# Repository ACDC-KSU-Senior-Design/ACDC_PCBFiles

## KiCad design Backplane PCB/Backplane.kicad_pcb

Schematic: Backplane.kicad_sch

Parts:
C1: .47u; C_0805_2012Metric
C2: 0.1u; C_0603_1608Metric
C3: 3.3n; C_0603_1608Metric
C4: 33u; C_1206_3216Metric
C5, C6: 22u; C_1206_3216Metric
C7, C8, C9, C10, C11, C12, C13, C14, C15, C16, C17, C18, C19, C20, C21, C22, C23: 10u; C_1206_3216Metric
CR1: SMDJ85A
CR6, CR8, CR10, CR12, CR14, CR16, CR18, CR19, CR20, CR24, CR25, CR26: SMDJ33A
CR27, CR28, CR29, CR30, CR31: SMDJ6.0A; SMDJ6_0A
CR32: RF201LAM2STR; RF201LAM2STR(new_POW_diode)
CR33, CR34, CR35, CR36, CR37, CR38, CR39, CR40, CR41, CR42, CR43, CR44: RBR1MM60ATFTR; RBR1MM60ATFTR(new_VR_diode)
D1: 1N5818; D_DO-41_SOD81_P10.16mm_Horizontal
D2, D3, D4, D5, D6, D7, D8, D9, D10, D11, D12, D15: 1N4148WS
D27, D28, D29, D30, D31, D32, D33, D34, D35, D36: 1N5819HW-7-F; 1N5819; PARTREV 18-2
D37, D38, D39, D40, D41, D42: SMDJ60CA; SMDJ6_0CA; PARTREV R2102
H1, H2, H3, H4, H5, H6, H7: MountingHole; MountingHole_3.2mm_M3
J1, J2, J3, J4, J5: 10018783-10202TLF; PCI_Express_Card; PARTREV AA
J6: 5019514000; BP_Connector
L1: 22u; IND_1210-WE-PD_WRE
R1, R4: 30k; R_0805_2012Metric
R2: 20m; R_1206_3216Metric
R3, R81: 200k; R_0805_2012Metric
R5, R7, R55, R56, R57, R58, R59, R60: 10k; R_0805_2012Metric
R6, R24: 15k; R_0805_2012Metric
R8, R10, R50, R51, R52, R53, R54: 100k; R_0805_2012Metric
R9, R11: 10; R_0805_2012Metric
R12, R69, R70, R71, R72, R73, R74, R75, R76, R77, R78, R79, R84: 2k; R_0805_2012Metric
R13, R15, R17, R19, R21, R23, R27, R29, R31, R33, R35, R37, R38, R39, R40, R41, R42, R43, R44, R45, R46, R47, R48, R49, R86, R87, R88, R89, R90, R92, R94, R95, R99, R100: 1k; R_0805_2012Metric
R14, R16, R18, R20, R22, R26, R28, R30, R32, R34, R36, R68, R83: 3k; R_0805_2012Metric
R25: 4.7k; R_0805_2012Metric
R61, R63: 2.2k; R_0805_2012Metric
R62, R64, R65: 200; R_0402_1005Metric
R66, R67: 2; R_0603_1608Metric
R80, R82: 22k; R_0805_2012Metric
R85: 1.5k; R_0805_2012Metric
U1: LTC3894EFE-PBF; TSSOP20-EP_4P4X6P5_ADI
U2: FDS4435A; SOIC8_751EB_FAS
U3, U4, U5, U6, U7, U8, U11, U12, U13, U14, U15, U16: ISP817CXSM; ISP817SM_ISO
U9, U10: ADP7104ACPZ-R7; CP_8_5_ADI
U17, U18, U19, U20, U21: OP191GSZ-REEL7; OP191

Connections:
3V3: C5.2, C8.1, C9.1, C10.1, C11.1, C12.1, C13.1, R6.2, R8.2, R9.2, U3.4, U4.4, U5.4, U6.4, U7.4, U8.4, U9.1 (VOUT)
5.5V: C6.2, C7.1, C20.1, C21.1, C22.1, C23.1, D28.C, D30.C, D32.C, D34.C, D36.C, R10.2, R11.2, R24.2, U10.1 (VOUT), U17.7 (+V), U18.7 (+V), U19.7 (+V), U20.7 (+V), U21.7 (+V)
28V_REF: C1.1, C14.1, C15.1, C16.1, C17.1, C18.1, C19.1, CR1.1, CR32.1, D2.C, D4.C, D6.C, D7.C, D9.C, D11.C, J6.17, R5.2, U1.3 (RUN), U1.20 (VIN), U2.8, U11.4, U12.4, U13.4, U14.4, U15.4, U16.4
A429_IN+: D38.2, J1.A11, J1.B11, J2.A11, J2.B11, J3.A11, J3.B11, J4.A11, J4.B11, J5.A11, J5.B11, J6.11, R56.2
A429_IN-: D37.2, J1.A10, J1.B10, J2.A10, J2.B10, J3.A10, J3.B10, J4.A10, J4.B10, J5.A10, J5.B10, J6.10, R55.2
A429_OUT+: D39.2, J1.A12, J1.B12, J2.A12, J2.B12, J3.A12, J3.B12, J4.A12, J4.B12, J5.A12, J5.B12, J6.12, R57.2
A429_OUT-: D40.2, J1.A13, J1.B13, J2.A13, J2.B13, J3.A13, J3.B13, J4.A13, J4.B13, J5.A13, J5.B13, J6.13, R58.2
BPOW: C4.1, J1.A17, J1.B17, J2.A17, J2.B17, J3.A17, J3.B17, J4.A17, J4.B17, J5.A17, J5.B17, R2.1, R3.2, U1.6 (SENSE-), U9.5 (EN/UVLO), U9.8 (VIN), U10.5 (EN/UVLO), U10.8 (VIN)
CANHI: J1.A7, J1.B7, J2.A7, J2.B7, J3.A7, J3.B7, J4.A7, J4.B7, J5.A7, J5.B7
CANLO: J1.A8, J1.B8, J2.A8, J2.B8, J3.A8, J3.B8, J4.A8, J4.B8, J5.A8, J5.B8
DAC_OUT: J1.A5, J1.B5, J2.A5, J2.B5, J3.A5, J3.B5, J4.A5, J4.B5, J5.A5, J5.B5, U21.2 (-INA), U21.6 (OUTA)
DI1: CR6.1, CR33.1, J6.19, R39.2, R68.2
DI2: CR10.1, CR34.1, J6.20, R14.2, R41.2
DI3: CR14.1, CR35.1, J6.21, R16.2, R43.2
DI4: CR8.1, CR36.1, J6.22, R18.2, R40.2
DI5: CR12.1, CR37.1, J6.23, R20.2, R42.2
DI6: CR16.1, CR38.1, J6.24, R22.2, R44.2
DO1: CR18.1, CR39.1, J6.27, R27.2, R38.2, U11.3
DO2: CR19.1, CR40.1, J6.28, R29.2, R45.2, U12.3
DO3: CR20.1, CR41.1, J6.29, R31.2, R46.2, U13.3
DO4: CR24.1, CR42.1, J6.30, R33.2, R47.2, U14.3
DO5: CR25.1, CR43.1, J6.31, R35.2, R48.2, U15.3
DO6: CR26.1, CR44.1, J6.32, R37.2, R49.2, U16.3
DOFB1: J1.A27, J1.B27, J2.A27, J2.B27, J3.A27, J3.B27, J4.A27, J4.B27, J5.A27, J5.B27, R26.2
DOFB2: J1.A28, J1.B28, J2.A28, J2.B28, J3.A28, J3.B28, J4.A28, J4.B28, J5.A28, J5.B28, R28.2
DOFB3: J1.A29, J1.B29, J2.A29, J2.B29, J3.A29, J3.B29, J4.A29, J4.B29, J5.A29, J5.B29, R30.2
DOFB4: J1.A30, J1.B30, J2.A30, J2.B30, J3.A30, J3.B30, J4.A30, J4.B30, J5.A30, J5.B30, R32.2
DOFB5: J1.A31, J1.B31, J2.A31, J2.B31, J3.A31, J3.B31, J4.A31, J4.B31, J5.A31, J5.B31, R34.2
DOFB6: J1.A32, J1.B32, J2.A32, J2.B32, J3.A32, J3.B32, J4.A32, J4.B32, J5.A32, J5.B32, R36.2
DSI1: J1.A19, J1.B19, J2.A19, J2.B19, J3.A19, J3.B19, J4.A19, J4.B19, J5.A19, J5.B19, R13.2, U3.3
DSI2: J1.A20, J1.B20, J2.A20, J2.B20, J3.A20, J3.B20, J4.A20, J4.B20, J5.A20, J5.B20, R15.2, U4.3
DSI3: J1.A21, J1.B21, J2.A21, J2.B21, J3.A21, J3.B21, J4.A21, J4.B21, J5.A21, J5.B21, R17.2, U5.3
DSI4: J1.A22, J1.B22, J2.A22, J2.B22, J3.A22, J3.B22, J4.A22, J4.B22, J5.A22, J5.B22, R19.2, U6.3
DSI5: J1.A23, J1.B23, J2.A23, J2.B23, J3.A23, J3.B23, J4.A23, J4.B23, J5.A23, J5.B23, R21.2, U7.3
DSI6: J1.A24, J1.B24, J2.A24, J2.B24, J3.A24, J3.B24, J4.A24, J4.B24, J5.A24, J5.B24, R23.2, U8.3
GND: C2.2, C3.2, C4.2, C5.1, C6.1, C7.2, C8.2, C9.2, C10.2, C11.2, C12.2, C13.2, C14.2, C15.2, C16.2, C17.2, C18.2, C19.2, C20.2, C21.2, C22.2, C23.2, CR1.2, CR6.2, CR8.2, CR10.2, CR12.2, CR14.2, CR16.2, CR18.2, CR19.2, CR20.2, CR24.2, CR25.2, CR26.2, CR27.2, CR28.2, CR29.2, CR30.2, CR31.2, CR32.2, CR33.2, CR34.2, CR35.2, CR36.2, CR37.2, CR38.2, CR39.2, CR40.2, CR41.2, CR42.2, CR43.2, CR44.2, D1.2 (A), D3.A, D5.A, D8.A, D10.A, D12.A, D15.A, D27.A, D29.A, D31.A, D33.A, D35.A, D37.1, D38.1, D39.1, D40.1, D41.1, D42.1, J1.A6, J1.A9, J1.A16, J1.A18, J1.A25, J1.A26, J1.A33, J1.B6, J1.B9, J1.B16, J1.B18, J1.B25, J1.B26, J1.B33, J2.A6, J2.A9, J2.A16, J2.A18, J2.A25, J2.A26, J2.A33, J2.B6, J2.B9, J2.B16, J2.B18, J2.B25, J2.B26, J2.B33, J3.A6, J3.A9, J3.A16, J3.A18, J3.A25, J3.A26, J3.A33, J3.B6, J3.B9, J3.B16, J3.B18, J3.B25, J3.B26, J3.B33, J4.A6, J4.A9, J4.A16, J4.A18, J4.A25, J4.A26, J4.A33, J4.B6, J4.B9, J4.B16, J4.B18, J4.B25, J4.B26, J4.B33, J5.A6, J5.A9, J5.A16, J5.A18, J5.A25, J5.A26, J5.A33, J5.B6, J5.B9, J5.B16, J5.B18, J5.B25, J5.B26, J6.6, J6.7, J6.8, J6.9, J6.16, J6.18, J6.25, J6.26, J6.33, R5.1, R7.1, R13.1, R15.1, R17.1, R19.1, R21.1, R23.1, R27.1, R29.1, R31.1, R33.1, R35.1, R37.1, R38.1, R39.1, R40.1, R41.1, R42.1, R43.1, R44.1, R45.1, R46.1, R47.1, R48.1, R49.1, R50.1, R51.1, R52.1, R53.1, R54.1, R55.1, R56.1, R57.1, R58.1, R59.1, R60.1, R65.1, R66.1, R67.1, R80.1, R85.2, R86.1, R87.1, R88.1, R89.1, R90.1, R92.1, R94.1, R95.1, R99.1, R100.1, U1.11 (PLLIN/MODE), U1.14 (OVLO), U1.15 (EXTS), U3.2, U4.2, U5.2, U6.2, U7.2, U8.2, U9.3 (GND), U9.6 (GND), U9.9 (EPAD), U10.3 (GND), U10.6 (GND), U10.9 (EPAD), U11.2, U12.2, U13.2, U14.2, U15.2, U16.2, U17.4 (-V), U18.4 (-V), U19.4 (-V), U20.4 (-V), U21.4 (-V)
unnamed: D1.1 (K), L1.2, U2.3
unnamed: D2.A, D3.C, R12.1, U3.1
unnamed: D4.A, D5.C, R70.1, U5.1
unnamed: D7.A, D8.C, R71.1, U6.1
unnamed: D9.A, D10.C, R72.1, U7.1
unnamed: D11.A, D12.C, R73.1, U8.1
unnamed: D6.A, D15.C, R69.1, U4.1
unnamed: D27.C, D28.A
unnamed: D29.C, D30.A
unnamed: D31.C, D32.A
unnamed: D33.C, D34.A
unnamed: D35.C, D36.A
unnamed: J1.A34, R86.2
unnamed: J1.A35, R87.2
unnamed: J1.A36, R88.2
unnamed: J2.A34, R89.2
unnamed: J2.A35, R90.2
unnamed: J3.A34, R92.2
unnamed: J3.A36, R94.2
unnamed: J4.A34, R95.2
unnamed: J5.A35, R99.2
unnamed: J5.A36, R100.2
unnamed: R1.2, R83.1
unnamed: R3.1, R81.2
unnamed: R4.1, R80.2
unnamed: R6.1, R61.2
unnamed: R11.1, R67.2
unnamed: R12.2, R68.1
unnamed: R14.1, R69.2
unnamed: R16.1, R70.2
unnamed: R18.1, R71.2
unnamed: R20.1, R72.2
unnamed: R22.1, R73.2
unnamed: R24.1, R63.2
unnamed: R25.1, R65.2
unnamed: R26.1, R79.2
unnamed: R28.1, R78.2
unnamed: R30.1, R77.2
unnamed: R32.1, R76.2
unnamed: R34.1, R75.2
unnamed: R36.1, R74.2
unnamed: R61.1, R62.2
unnamed: R63.1, R64.2
unnamed: R9.1, R66.2
unnamed: R74.1, U16.1
unnamed: R75.1, U15.1
unnamed: R76.1, U14.1
unnamed: R77.1, U13.1
unnamed: R78.1, U12.1
unnamed: R79.1, U11.1
unnamed: R81.1, R82.2
unnamed: R83.2, R84.1
unnamed: R84.2, R85.1
unnamed: C1.2, U1.18 (CAP)
unnamed: R1.1, U1.13 (FREQ)
unnamed: U1.1 (GATE), U2.4
unnamed: C3.1, U1.7 (ITH)
unnamed: R4.2, R82.1, U1.8 (PGUV), U1.9 (VFB)
unnamed: L1.1, R2.2, U1.5 (SENSE+)
unnamed: C2.1, U1.10 (TRACK/SS)
unnamed: R8.1, U9.7 (PG)
unnamed: R7.2, R62.1, U9.2 (SENSE/ADJ)
unnamed: R10.1, U10.7 (PG)
unnamed: R25.2, R64.1, U10.2 (SENSE/ADJ)
unnamed: CR27.1, J6.1, R50.2, U17.3 (+INA)
unnamed: CR28.1, J6.2, R51.2, U18.3 (+INA)
unnamed: CR29.1, J6.3, R52.2, U19.3 (+INA)
unnamed: CR30.1, J6.4, R53.2, U20.3 (+INA)
unnamed: CR31.1, J6.5, R54.2, U21.3 (+INA)
RTD+IN: J1.A4, J1.B4, J2.A4, J2.B4, J3.A4, J3.B4, J4.A4, J4.B4, J5.A4, J5.B4, U20.2 (-INA), U20.6 (OUTA)
RTD-IN: J1.A3, J1.B3, J2.A3, J2.B3, J3.A3, J3.B3, J4.A3, J4.B3, J5.A3, J5.B3, U19.2 (-INA), U19.6 (OUTA)
SIN1: D41.2, J1.A14, J1.B14, J2.A14, J2.B14, J3.A14, J3.B14, J4.A14, J4.B14, J5.A14, J5.B14, J6.14, R59.2
SIN2: D42.2, J1.A15, J1.B15, J2.A15, J2.B15, J3.A15, J3.B15, J4.A15, J4.B15, J5.A15, J5.B15, J6.15, R60.2
TD+IN: J1.A2, J1.B2, J2.A2, J2.B2, J3.A2, J3.B2, J4.A2, J4.B2, J5.A2, J5.B2, U18.2 (-INA), U18.6 (OUTA)
TD-IN: J1.A1, J1.B1, J2.A1, J2.B1, J3.A1, J3.B1, J4.A1, J4.B1, J5.A1, J5.B1, U17.2 (-INA), U17.6 (OUTA)

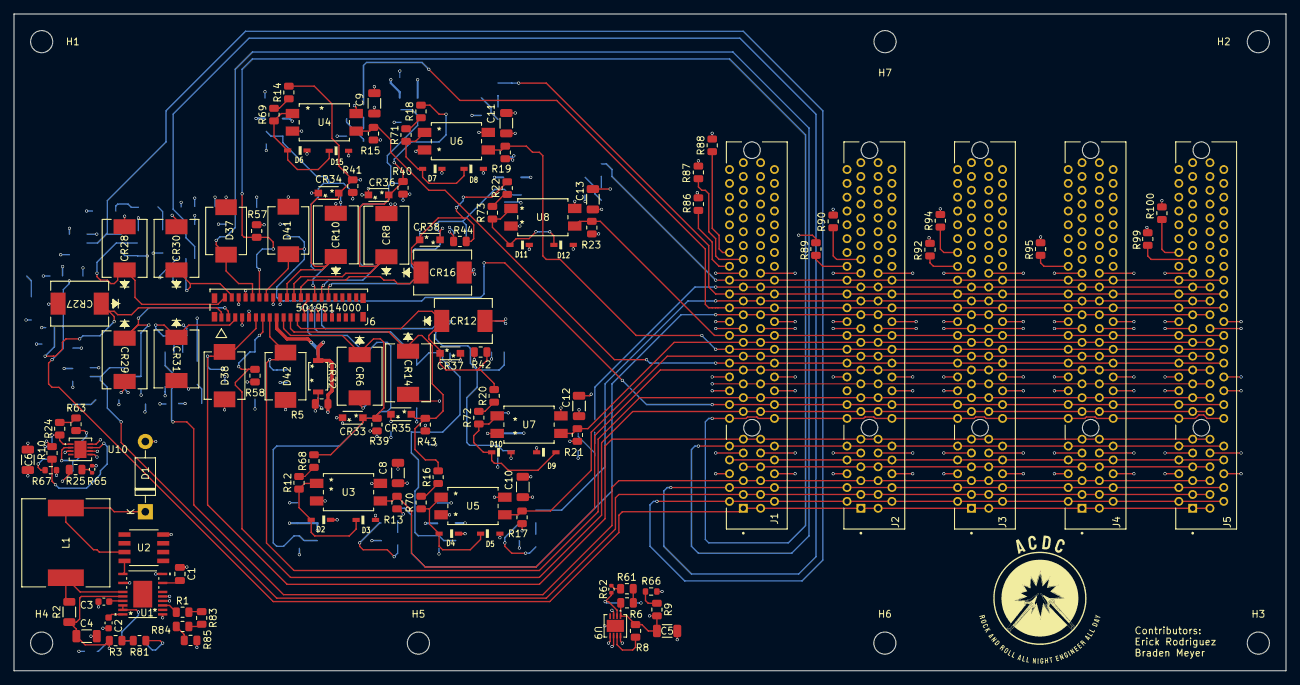
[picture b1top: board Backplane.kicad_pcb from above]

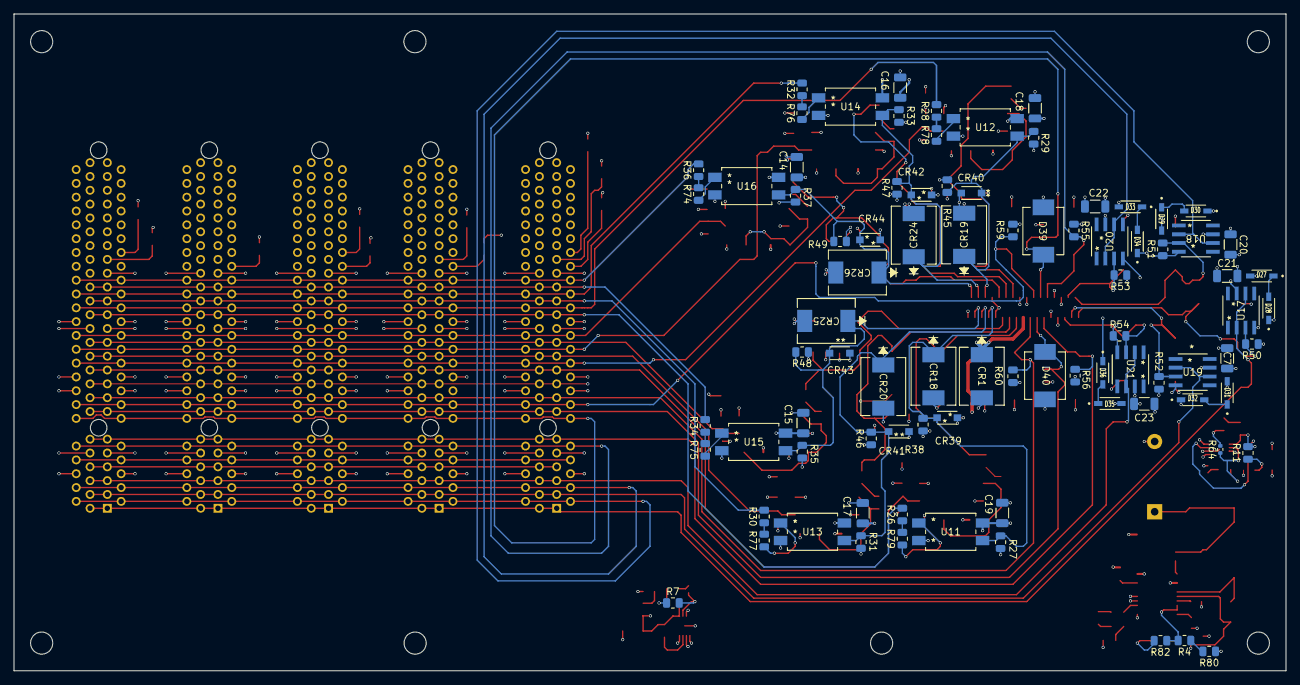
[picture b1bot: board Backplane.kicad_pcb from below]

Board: 4 copper layers, 184.0 x 95.0 mm, 213 parts (86 on the bottom side), 111 nets.

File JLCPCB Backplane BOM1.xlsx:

Comment | Designator | Footprint | JLCPCB Part #（optional）
3.3nF | C3 | C_0603_1608Metric | C1613
.47uF | C1 | C_0805_2012Metric | C13967
0.1uF | C2 | C_0603_1608Metric | C14663
10uF | C10,C8,C11,C9,C13,C12,C15,C22,C7,C16,C20,C19,C23,C14,C21,C18,C17 | C_1206_3216Metric | C13585
22uF | C6,C5 | C_1206_3216Metric | C12891
33uF | C4 | C_1206_3216Metric | C524627
20m | R2 | R_1206_3216Metric | C2765435
2 | R67,R66 | R_0603_1608Metric | C22977
10 | R9,R11 | R_0805_2012Metric | C17415
200 | R62,R65,R64 | R_0402_1005Metric | C25087
1k | R38,R39,R40,R41,R42,R43,R44,R45,R46,R47,R48,R49, R99,R94,R13,R23,R100,R88,R17,R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 | R_0805_2012Metric | C17513
1.5k | R85 | R_0805_2012Metric | C4310
2k | R71,R72,R70,R84,R69,R12,R73,R74,R75,R77,R79,R76,R78 | R_0805_2012Metric | C17604
2.2k | R63,R61 | R_0805_2012Metric | C17520
3k | R18,R20,R22,R16,R68,R83,R14,R32,R34,R30,R28,R26,R36 | R_0805_2012Metric | C17661
4.7k | R25 | R_0805_2012Metric | C17673
10k | R7,R5,R58,R57,R55,R56,R60,R59 | R_0805_2012Metric | C174414
15k | R24,R6 | R_0805_2012Metric | C17475
22k | R82,R80 | R_0805_2012Metric | C17560
30k | R1,R4 | R_0805_2012Metric | C17621
100k | R10,R8,R50,R51,R54,R52,R53 | R_0805_2012Metric | C149504
200k | R81,R3 | R_0805_2012Metric | C17539
22uH | L1 | 22uH_IND
5019514000 | J6 | BP_Connector | C493441
1N4148WS | D8,D4,D11,D5,D12,D3,D7,D10,D6,D15,D9,D2 | 1N4148WS | C2128
1N5818 | D1 | D_DO-41_SOD81_P10.16mm_Horizontal | C402217
1N5819HW-7-F | D34,D29,D28,D33,D30,D31,D35,D27,D36,D32 | 1N5819 | C82544
ADP7104ACPZ-R7 | U9,U10 | CP_8_5_ADI | C514351
FDS4435A | U2 | SOIC8_751EB_FAS | C5122021
LTC3894EFE-PBF | U1 | TSSOP20-EP_4P4X6P5_ADI | C580815
RF201LAM2STR | CR32 | RF201LAM2STR(new_POW_diode) | C509969
SMDJ33A | CR16,CR6,CR8,CR10,CR14,CR12,CR25,CR19,CR24,CR26,CR20,CR18 | SMDJ33A | C438163
SMDJ6.0A | CR31,CR27,CR30,CR28,CR29 | SMDJ6_0A | C152070
SMDJ6.0CA | D38,D41,D42,D37,D40,D39 | SMDJ6_0CA | C310142
SMDJ85A | CR1 | SMDJ85A | C2990381
LTV-816S-TA1-B | U6,U5,U7,U3,U4,U8,U12,U16,U13,U15,U14,U11 | ISP817SM_ISO | C115456
OP191GSZ-REEL7 | U17,U21,U19,U18,U20 | OP191
RBR1MM60ATFTR | CR35,CR38,CR36,CR37,CR33,CR34,CR43,CR44,CR41,CR39,CR42,CR40 | RBR1MM60ATFTR(new_VR_diode)
10018783-10202TLF | J5,J1,J2,J4,J3 | PCI_Express_Card

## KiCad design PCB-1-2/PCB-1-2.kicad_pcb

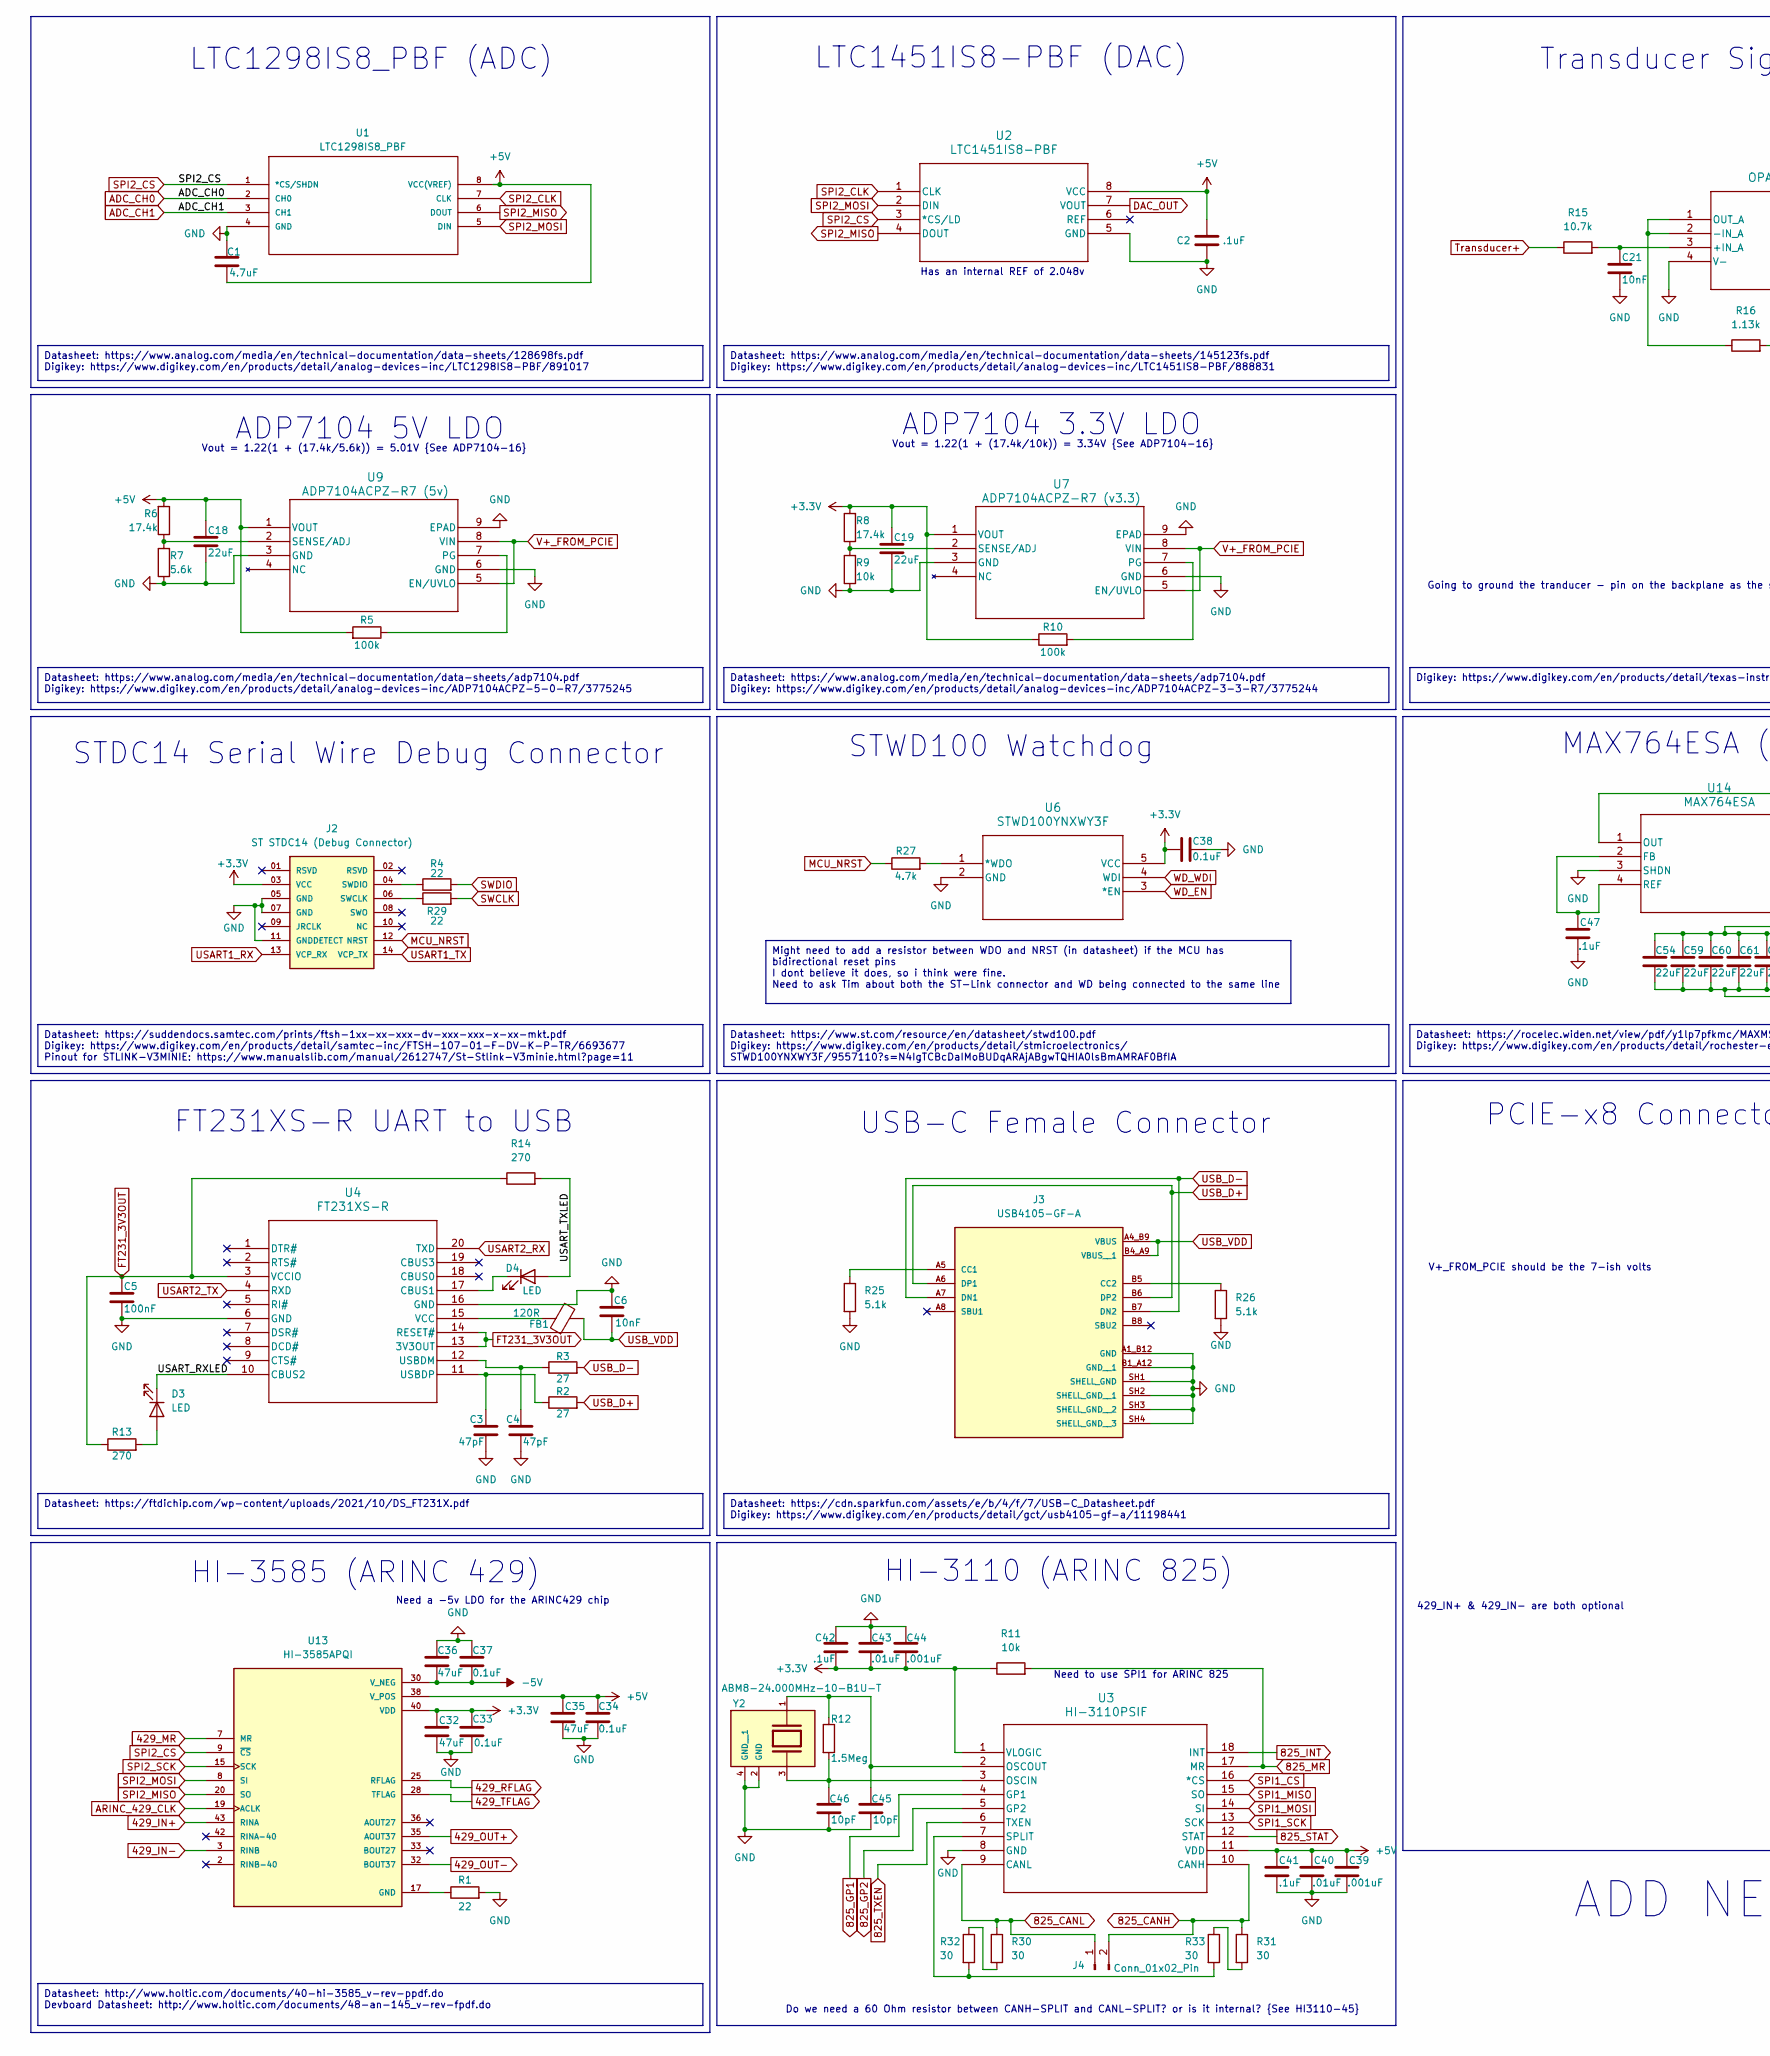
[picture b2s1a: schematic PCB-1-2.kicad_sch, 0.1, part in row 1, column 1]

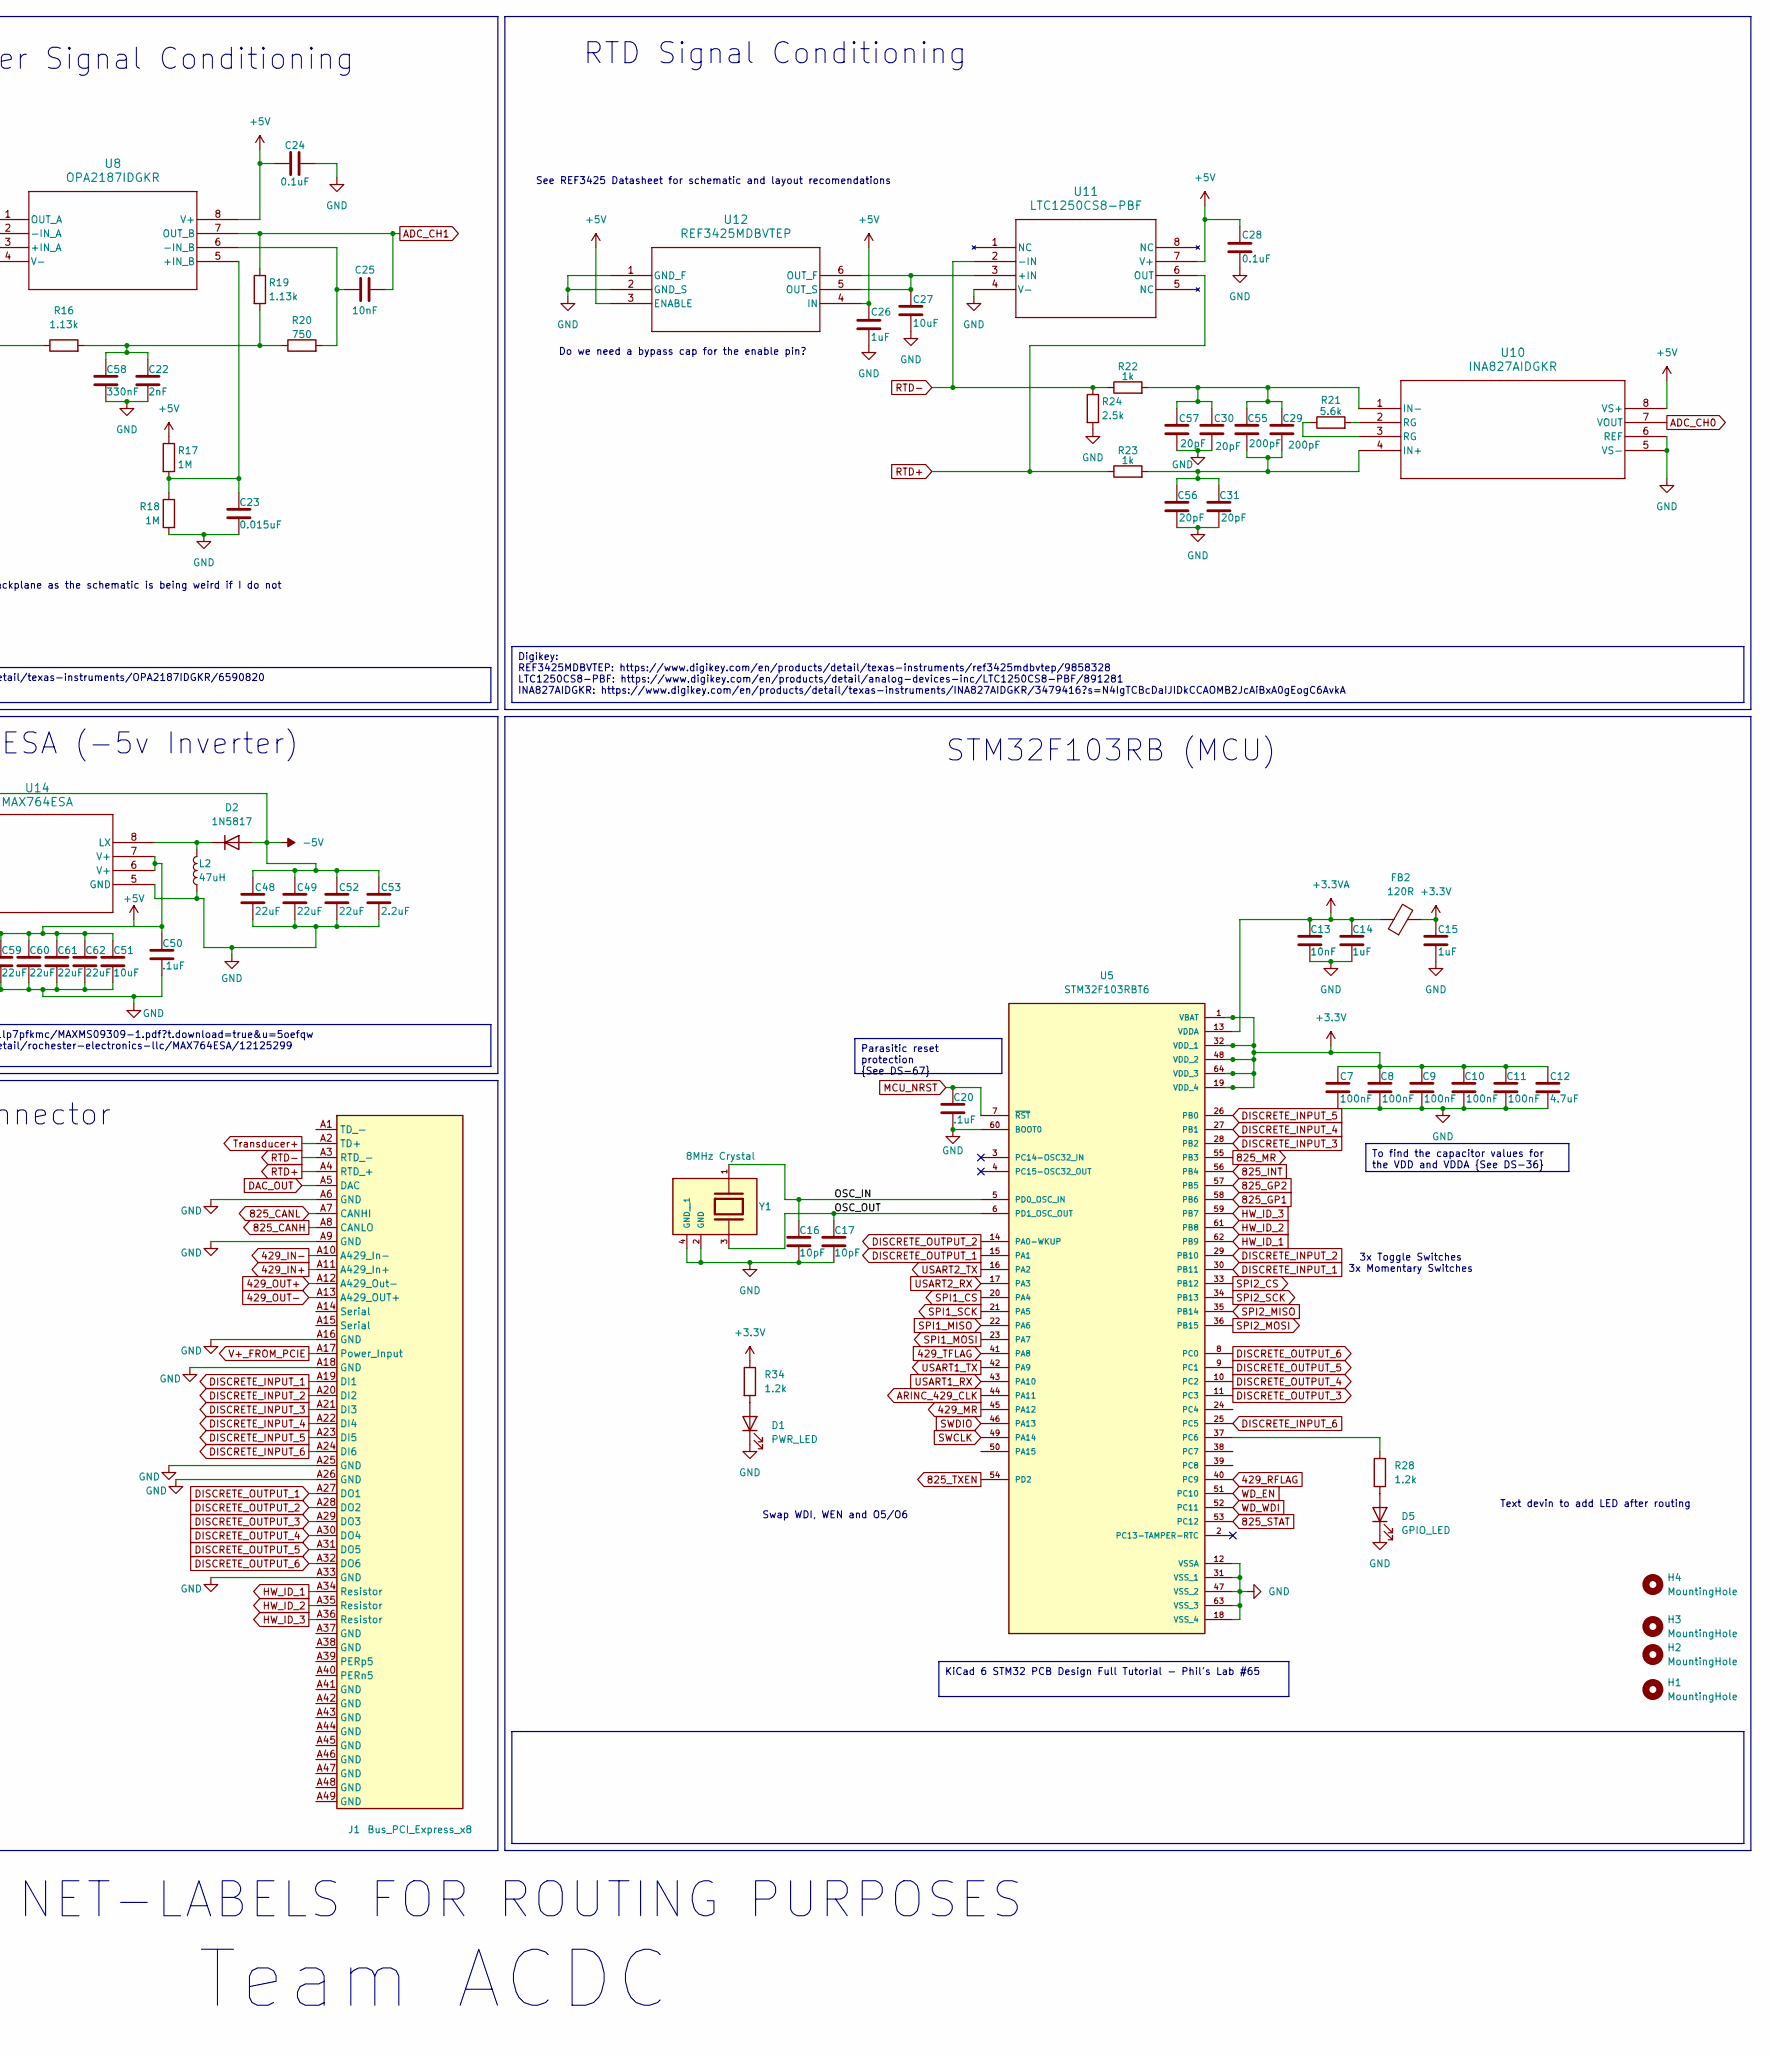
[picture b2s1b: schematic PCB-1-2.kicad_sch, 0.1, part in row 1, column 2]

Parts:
C1, C12: 4.7uF; C_0805_2012Metric
C2, C20, C41, C42: .1uF; C_0805_2012Metric
C3, C4: 47pF; C_0805_2012Metric
C5, C7, C8, C9, C10, C11: 100nF; C_0805_2012Metric
C6, C13, C21, C25: 10nF; C_0805_2012Metric
C14, C15, C26: 1uF; C_0805_2012Metric
C16, C17, C45, C46: 10pF; C_0805_2012Metric
C18, C19, C48, C49, C52, C54, C59, C60, C61, C62: 22uF; C_0805_2012Metric
C22: 2nF; C_0603_1608Metric
C23: 0.015uF; C_0402_1005Metric
C24, C28, C33, C34, C37, C38: 0.1uF; C_0805_2012Metric
C27: 10uF; C_0805_2012Metric
C29, C55: 200pF; C_0603_1608Metric
C30, C31, C56, C57: 20pF; C_0805_2012Metric
C32, C35, C36: 47uF; C_0805_2012Metric
C39, C44: .001uF; C_0805_2012Metric
C40, C43: .01uF; C_0805_2012Metric
C47, C50: .1uF; C_0603_1608Metric
C51: 10uF; C_1206_3216Metric
C53: 2.2uF; C_0805_2012Metric
C58: 330nF; C_0805_2012Metric
D1: PWR_LED; LED_0805_2012Metric
D2: 1N5817
D3, D4: LED; LED_0805_2012Metric
D5: GPIO_LED; LED_0805_2012Metric
FB1, FB2: 120R; L_0805_2012Metric
H1, H2, H3, H4: MountingHole; MountingHole_2.2mm_M2
J1: Bus_PCI_Express_x8; BUS_PCIexpress_x8
J2: ST STDC14 (Debug Connector); SAMTEC_FTSH-107-01-F-DV-K-P-TR; PARTREV R
J3: USB4105-GF-A; GCT_USB4105-GF-A; PARTREV B3
J4: Conn_01x02_Pin; pin header
L2: 47uH; L_0805_2012Metric
R1, R4, R29: 22; R_0805_2012Metric
R2, R3: 27; R_0805_2012Metric
R5, R10: 100k; R_0805_2012Metric
R6, R8: 17.4k; R_0805_2012Metric
R7, R21: 5.6k; R_0805_2012Metric
R9, R11: 10k; R_0805_2012Metric
R12: 1.5Meg; R_0805_2012Metric
R13, R14: 270; R_0805_2012Metric
R15: 10.7k; R_0805_2012Metric
R16, R19: 1.13k; R_0805_2012Metric
R17, R18: 1M; R_0805_2012Metric
R20: 750; R_0805_2012Metric
R22, R23: 1k; R_0805_2012Metric
R24: 2.5k; R_0805_2012Metric
R25, R26: 5.1k; R_0805_2012Metric
R27: 4.7k; R_0805_2012Metric
R28, R34: 1.2k; R_0805_2012Metric
R30, R31, R32, R33: 30; R_0603_1608Metric
U1: LTC1298IS8_PBF; SOIC-8_S; MANUFACTURER_PART_NUMBER ltc1298is8#pbf
U2: LTC1451IS8-PBF; SO-8_S_LIT
U3: HI-3110PSIF; SOIC-18WB_HIC
U4: FT231XS-R; FT231XS-R_FTD
U5: STM32F103RBT6; QFP50P1200X1200X160-64N; PARTREV 18
U6: STWD100YNXWY3F; SOT23-5_STM
U7: ADP7104ACPZ-R7 (v3.3); CP_8_5_ADI
U8: OPA2187IDGKR; DGK8_TEX
U9: ADP7104ACPZ-R7 (5v); CP_8_5_ADI
U10: INA827AIDGKR; DGK8_TEX
U11: LTC1250CS8-PBF; SO-8_S_LIT
U12: REF3425MDBVTEP; SOT-23-6_TEX
U13: HI-3585APQI; QFP80P1390X1390X150-44N; PARTREV C
U14: MAX764ESA; SO-G8_1_MXM
Y1: 8MHz Crystal; XTAL_ABM3B-8.000MHZ-10-1-U-T; PARTREV 08.25.15
Y2: ABM8-24.000MHz-10-B1U-T; XTAL_ABM8-24.000MHz-10-B1U-T; PARTREV 44041

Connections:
429_IN+: J1.A11 (A429_In+), U13.43 (RINA)
429_IN-: J1.A10 (A429_In-), U13.3 (RINB)
429_MR: U5.45 (PA12), U13.7 (MR)
429_OUT+: J1.A12 (A429_Out-), U13.35 (AOUT37)
429_OUT-: J1.A13 (A429_OUT+), U13.32 (BOUT37)
429_RFLAG: U5.40 (PC9), U13.25 (RFLAG)
429_TFLAG: U5.41 (PA8), U13.28 (TFLAG)
825_CANH: J1.A8 (CANLO), J4.2, R31.1, U3.10 (CANH)
825_CANL: J1.A7 (CANHI), J4.1, R30.1, U3.9 (CANL)
825_GP1: U3.4 (GP1), U5.58 (PB6)
825_GP2: U3.5 (GP2), U5.57 (PB5)
825_INT: U3.18 (INT), U5.56 (PB4)
825_MR: R11.2, U3.17 (MR), U5.55 (PB3)
825_STAT: U3.12 (STAT), U5.53 (PC12)
825_TXEN: U3.6 (TXEN), U5.54 (PD2)
+3.3V: C7.2, C8.2, C9.2, C10.2, C11.2, C12.2, C15.1, C19.1, C32.1, C33.1, C38.2, C42.2, C43.2, C44.2, FB2.2, J2.03 (VCC), R8.2, R10.1, R11.1, R34.1, U3.1 (VLOGIC), U5.1 (VBAT), U5.19 (VDD_4), U5.32 (VDD_1), U5.48 (VDD_2), U5.64 (VDD_3), U6.5 (VCC), U7.1 (VOUT), U13.40 (VDD)
+3.3VA: C13.1, C14.1, FB2.1, U5.13 (VDDA)
+5V: C1.1, C2.1, C18.1, C24.2, C26.1, C28.1, C34.1, C35.1, C39.1, C40.1, C41.1, C50.1, C51.1, C54.1, C59.1, C60.1, C61.1, C62.1, R5.2, R6.2, R17.1, U1.8 (VCC(VREF)), U2.8 (VCC), U3.11 (VDD), U8.8 (V+), U9.1 (VOUT), U10.8 (VS+), U11.7 (V+), U12.3 (ENABLE), U12.4 (IN), U13.38 (V_POS), U14.6 (V+), U14.7 (V+)
-5V: C36.2, C37.2, C48.1, C49.1, C52.1, C53.1, D2.2 (A), U13.30 (V_NEG), U14.1 (OUT)
/OSC_IN: C16.1, U5.5 (PD0_OSC_IN), Y1.1
/OSC_OUT: C17.1, U5.6 (PD1_OSC_OUT), Y1.3
/USART_RXLED: D3.1 (K), U4.10 (CBUS2)
/USART_TXLED: D4.2 (A), R14.2
ADC_CH0: U1.2 (CH0), U10.7 (VOUT)
ADC_CH1: C25.2, R19.1, U1.3 (CH1), U8.7 (OUT_B)
ARINC_429_CLK: U5.44 (PA11), U13.19 (ACLK)
DAC_OUT: J1.A5 (DAC), U2.7 (VOUT)
DISCRETE_INPUT_1: J1.A19 (DI1), U5.30 (PB11)
DISCRETE_INPUT_2: J1.A20 (DI2), U5.29 (PB10)
DISCRETE_INPUT_3: J1.A21 (DI3), U5.28 (PB2)
DISCRETE_INPUT_4: J1.A22 (DI4), U5.27 (PB1)
DISCRETE_INPUT_5: J1.A23 (DI5), U5.26 (PB0)
DISCRETE_INPUT_6: J1.A24 (DI6), U5.25 (PC5)
DISCRETE_OUTPUT_1: J1.A27 (DO1), U5.15 (PA1)
DISCRETE_OUTPUT_2: J1.A28 (DO2), U5.14 (PA0-WKUP)
DISCRETE_OUTPUT_3: J1.A29 (DO3), U5.11 (PC3)
DISCRETE_OUTPUT_4: J1.A30 (DO4), U5.10 (PC2)
DISCRETE_OUTPUT_5: J1.A31 (DO5), U5.9 (PC1)
DISCRETE_OUTPUT_6: J1.A32 (DO6), U5.8 (PC0)
FT231_3V3OUT: C5.1, R13.1, R14.1, U4.3 (VCCIO), U4.13 (3V3OUT), U4.14 (RESET#)
GND: C1.2, C2.2, C3.2, C4.2, C5.2, C6.1, C7.1, C8.1, C9.1, C10.1, C11.1, C12.1, C13.2, C14.2, C15.2, C16.2, C17.2, C18.2, C19.2, C20.2, C21.2, C22.2, C23.2, C24.1, C26.2, C27.2, C28.2, C30.2, C31.2, C32.2, C33.2, C34.2, C35.2, C36.1, C37.1, C38.1, C39.2, C40.2, C41.2, C42.1, C43.1, C44.1, C45.2, C46.2, C47.2, C48.2, C49.2, C50.2, C51.2, C52.2, C53.2, C54.2, C56.2, C57.2, C58.2, C59.2, C60.2, C61.2, C62.2, D1.1 (K), D5.1 (K), J1.A6 (GND), J1.A9 (GND), J1.A16 (GND), J1.A18 (GND), J1.A25 (GND), J1.A26 (GND), J1.A33 (GND), J1.B4 (GND), J2.05 (GND), J2.07 (GND), J2.11 (GNDDETECT), J3.A1_B12 (GND), J3.B1_A12 (GND__1), J3.SH1 (SHELL_GND), J3.SH2 (SHELL_GND__1), J3.SH3 (SHELL_GND__2), J3.SH4 (SHELL_GND__3), L2.1, R1.2, R7.1, R9.1, R18.2, R24.2, R25.2, R26.2, U1.4 (GND), U2.5 (GND), U3.8 (GND), U4.6 (GND), U4.16 (GND), U5.12 (VSSA), U5.18 (VSS_4), U5.31 (VSS_1), U5.47 (VSS_2), U5.60 (BOOT0), U5.63 (VSS_3), U6.2 (GND), U7.3 (GND), U7.6 (GND), U7.9 (EPAD), U8.4 (V-), U9.3 (GND), U9.6 (GND), U9.9 (EPAD), U10.5 (VS-), U10.6 (REF), U11.4 (V-), U12.1 (GND_F), U12.2 (GND_S), U14.3 (SHDN), U14.5 (GND), Y1.2 (GND), Y1.4 (GND__1), Y2.2 (GND), Y2.4 (GND__1)
HW_ID_1: J1.A34 (Resistor), U5.62 (PB9)
HW_ID_2: J1.A35 (Resistor), U5.61 (PB8)
HW_ID_3: J1.A36 (Resistor), U5.59 (PB7)
MCU_NRST: C20.1, J2.12 (NRST), R27.1, U5.7 (~RST)
NC: J1.B1 (NC), J1.B8 (NC), J1.B10 (NC)
unnamed: C22.1, C58.1, R16.2, R19.2, R20.1
unnamed: D1.2 (A), R34.2
unnamed: D2.1 (K), L2.2, U14.8 (LX)
unnamed: D3.2 (A), R13.2
unnamed: D4.1 (K), U4.17 (CBUS1)
unnamed: D5.2 (A), R28.2
unnamed: J2.06 (SWCLK), R29.1
unnamed: J2.04 (SWDIO), R4.1
unnamed: J3.A5 (CC1), R25.1
unnamed: J3.B5 (CC2), R26.1
unnamed: R21.1, U10.3 (RG)
unnamed: R21.2, U10.2 (RG)
unnamed: R30.2, R32.1
unnamed: R31.2, R33.1
unnamed: C46.1, R12.2, U3.3 (OSCIN), Y2.3
unnamed: C45.1, R12.1, U3.2 (OSCOUT), Y2.1
unnamed: R32.2, R33.2, U3.7 (SPLIT)
unnamed: C4.1, R3.1, U4.12 (USBDM)
unnamed: C3.1, R2.1, U4.11 (USBDP)
unnamed: FB1.1, U4.15 (VCC)
unnamed: R28.1, U5.37 (PC6)
unnamed: R27.2, U6.1 (*WDO)
unnamed: R10.2, U7.7 (PG)
unnamed: R8.1, R9.2, U7.2 (SENSE/ADJ)
unnamed: C21.1, R15.2, U8.3 (+IN_A)
unnamed: C23.1, R17.2, R18.1, U8.5 (+IN_B)
unnamed: R16.1, U8.1 (OUT_A), U8.2 (-IN_A)
unnamed: C25.1, R20.2, U8.6 (-IN_B)
unnamed: R5.1, U9.7 (PG)
unnamed: R6.1, R7.2, U9.2 (SENSE/ADJ)
unnamed: C29.2, C31.1, C55.2, C56.1, R23.2, U10.4 (IN+)
unnamed: C29.1, C30.1, C55.1, C57.1, R22.2, U10.1 (IN-)
unnamed: C27.1, U11.3 (+IN), U12.5 (OUT_S), U12.6 (OUT_F)
unnamed: R1.1, U13.17 (GND)
unnamed: C47.1, U14.2 (FB), U14.4 (REF)
RTD+: J1.A4 (RTD_+), R23.1, U11.6 (OUT)
RTD-: J1.A3 (RTD_-), R22.1, R24.1, U11.2 (-IN)
SPI1_CS: U3.16 (*CS), U5.20 (PA4)
SPI1_MISO: U3.15 (SO), U5.22 (PA6)
SPI1_MOSI: U3.14 (SI), U5.23 (PA7)
SPI1_SCK: U3.13 (SCK), U5.21 (PA5)
SPI2_CLK: U1.7 (CLK), U2.1 (CLK)
SPI2_CS: U1.1 (*CS/SHDN), U2.3 (*CS/LD), U5.33 (PB12), U13.9 (~CS)
SPI2_MISO: U1.6 (DOUT), U2.4 (DOUT), U5.35 (PB14), U13.20 (SO)
SPI2_MOSI: U1.5 (DIN), U2.2 (DIN), U5.36 (PB15), U13.8 (SI)
SPI2_SCK: U5.34 (PB13), U13.15 (SCK)
SWCLK: R29.2, U5.49 (PA14)
SWDIO: R4.2, U5.46 (PA13)
Transducer+: J1.A2 (TD+), R15.1
USART1_RX: J2.13 (VCP_RX), U5.43 (PA10)
USART1_TX: J2.14 (VCP_TX), U5.42 (PA9)
USART2_RX: U4.20 (TXD), U5.17 (PA3)
USART2_TX: U4.4 (RXD), U5.16 (PA2)
USB_D+: J3.A6 (DP1), J3.B6 (DP2), R2.2
USB_D-: J3.A7 (DN1), J3.B7 (DN2), R3.2
USB_VDD: C6.2, FB1.2, J3.A4_B9 (VBUS), J3.B4_A9 (VBUS__1)
V+_FROM_PCIE: J1.A17 (Power_Input), U7.5 (EN/UVLO), U7.8 (VIN), U9.5 (EN/UVLO), U9.8 (VIN)
WD_EN: U5.51 (PC10), U6.3 (*EN)
WD_WDI: U5.52 (PC11), U6.4 (WDI)

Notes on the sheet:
Parasitic reset protection {See DS-67}
Datasheet: http://www.holtic.com/documents/40-hi-3585_v-rev-ppdf.do Devboard Datasheet: http://www.holtic.com/documents/48-an-145_v-rev-fpdf.do
Datasheet: https://suddendocs.samtec.com/prints/ftsh-1xx-xx-xxx-dv-xxx-xxx-x-xx-mkt.pdf Digikey: https://www.digikey.com/en/products/detail/samtec-inc/FTSH-107-01-F-DV-K-P-TR/6693677 Pinout for STLINK-V3MINIE: https://www.manualslib.com/manual/2612747/St-Stlink-V3minie.html?page=11
Datasheet: https://cdn.sparkfun.com/assets/e/b/4/f/7/USB-C_Datasheet.pdf Digikey: https://www.digikey.com/en/products/detail/gct/usb4105-gf-a/11198441
Digikey: REF3425MDBVTEP: https://www.digikey.com/en/products/detail/texas-instruments/ref3425mdbvtep/9858328 LTC1250CS8-PBF: https://www.digikey.com/en/products/detail/analog-devices-inc/LTC1250CS8-PBF/891281 INA827AIDGKR: https://www.digikey.com/en/products/detail/texas-instruments/INA827AIDGKR/34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
Digikey: https://www.digikey.com/en/products/detail/texas-instruments/OPA2187IDGKR/6590820
Datasheet: https://ftdichip.com/wp-content/uploads/2021/10/DS_FT231X.pdf
Datasheet: https://rocelec.widen.net/view/pdf/y1lp7pfkmc/MAXMS09309-1.pdf?t.download=true&u=5oefqw Digikey: https://www.digikey.com/en/products/detail/rochester-electronics-llc/MAX764ESA/12125299
Datasheet: https://www.analog.com/media/en/technical-documentation/data-sheets/adp7104.pdf Digikey: https://www.digikey.com/en/products/detail/analog-devices-inc/ADP7104ACPZ-5-0-R7/3775245
Might need to add a resistor between WDO and NRST (in datasheet) if the MCU has bidirectional reset pins I dont believe it does, so i think were fine. Need to ask Tim about both the ST-Link connector and WD being connected to the same line
Datasheet: https://www.analog.com/media/en/technical-documentation/data-sheets/adp7104.pdf Digikey: https://www.digikey.com/en/products/detail/analog-devices-inc/ADP7104ACPZ-3-3-R7/3775244
Datasheet: https://www.analog.com/media/en/technical-documentation/data-sheets/145123fs.pdf Digikey: https://www.digikey.com/en/products/detail/analog-devices-inc/LTC1451IS8-PBF/888831
KiCad 6 STM32 PCB Design Full Tutorial - Phil's Lab #65
Datasheet: https://www.analog.com/media/en/technical-documentation/data-sheets/128698fs.pdf Digikey: https://www.digikey.com/en/products/detail/analog-devices-inc/LTC1298IS8-PBF/891017
Datasheet: https://www.st.com/resource/en/datasheet/stwd100.pdf Digikey: https://www.digikey.com/en/products/detail/stmicroelectronics/ STWD100YNXWY3F/9557110?s=N4IgTCBcDaIMoBUDqARAjABgwTQHIA0lsBmAMRAF0BfIA
To find the capacitor values for the VDD and VDDA {See DS-36}
Transducer Signal Conditioning
STDC14 Serial Wire Debug Connector
429_IN+ & 429_IN- are both optional
Do we need a bypass cap for the enable pin?
STM32F103RB (MCU)
LTC1298IS8_PBF (ADC)
Need to use SPI1 for ARINC 825
Vout = 1.22(1 + (17.4k/10k)) = 3.34V {See ADP7104-16}
V+_FROM_PCIE should be the 7-ish volts
3x Toggle Switches 3x Momentary Switches
Going to ground the tranducer - pin on the backplane as the schematic is being weird if I do not
RTD Signal Conditioning
STWD100 Watchdog
ADD NET-LABELS FOR ROUTING PURPOSES
See REF3425 Datasheet for schematic and layout recomendations
USB-C Female Connector
LTC1451IS8-PBF (DAC)
FT231XS-R UART to USB
ADP7104 5V LDO
HI-3110 (ARINC 825)
Team ACDC
Vout = 1.22(1 + (17.4k/5.6k)) = 5.01V {See ADP7104-16}
Need a -5v LDO for the ARINC429 chip
PCIE-x8 Connector
